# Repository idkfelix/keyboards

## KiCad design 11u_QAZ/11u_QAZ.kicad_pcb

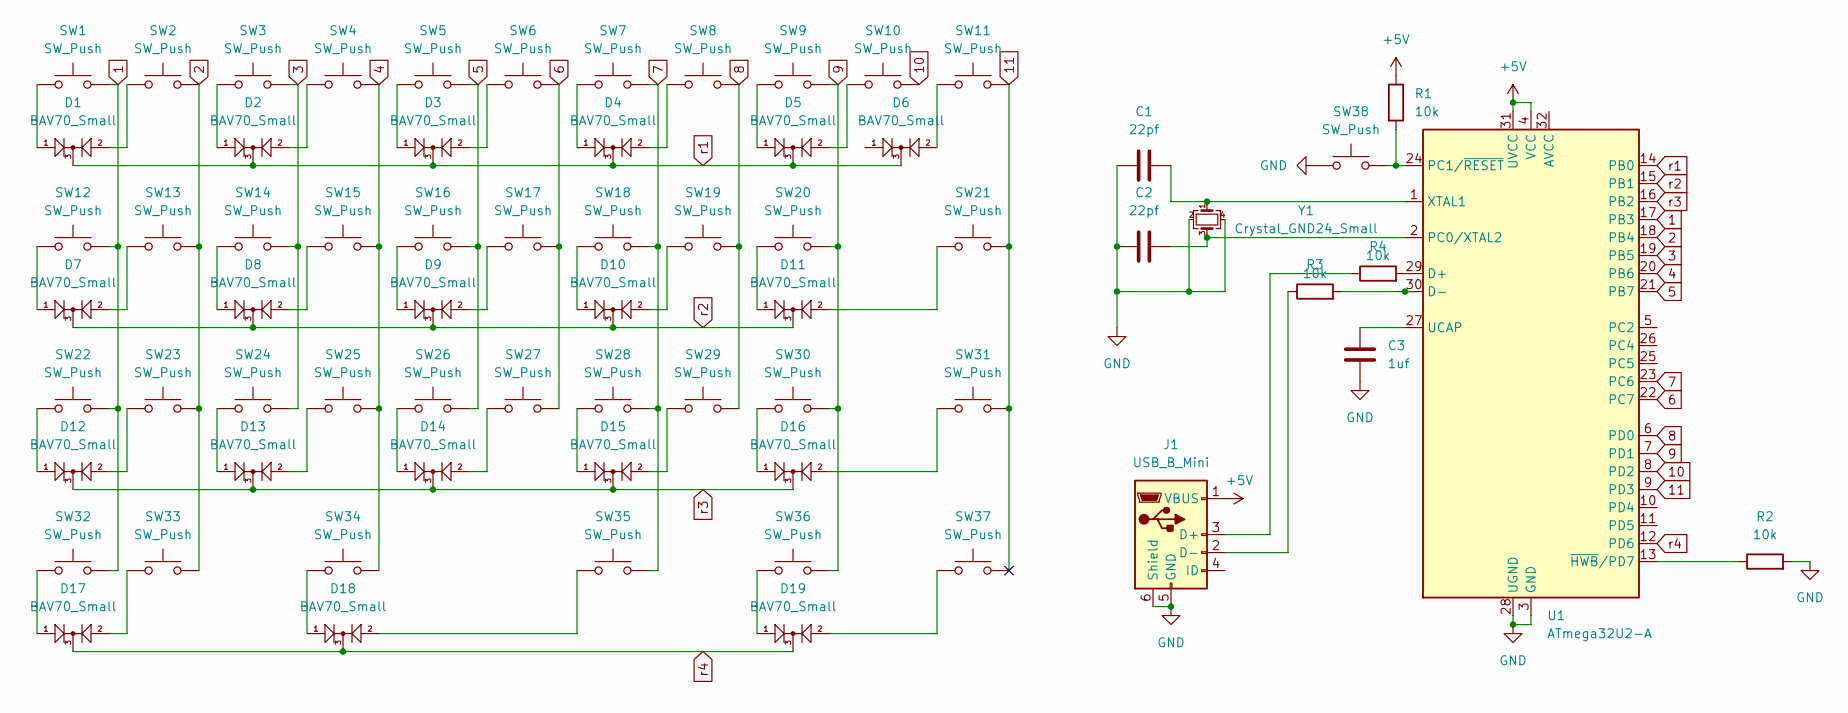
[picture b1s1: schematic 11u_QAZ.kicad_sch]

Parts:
C1, C2: 22pf; C_0805_2012Metric_Pad1.18x1.45mm_HandSolder
C3: 1uf; C_0805_2012Metric_Pad1.18x1.45mm_HandSolder
D1, D2, D3, D4, D5, D6, D7, D8, D9, D10, D11, D12, D13, D14, D15, D16, D17, D18, D19: BAV70_Small; SOT-23
J1: USB_B_Mini; Molex-0548190589
R1, R2, R3, R4: 10k; R_0805_2012Metric_Pad1.20x1.40mm_HandSolder
SW1, SW2, SW3, SW4, SW5, SW6, SW7, SW8, SW9, SW10, SW11, SW13, SW14, SW15, SW16, SW17, SW18, SW19, SW20, SW23, SW24, SW25, SW26, SW27, SW28, SW29, SW30: SW_Push; MX_1U
SW12, SW32, SW33, SW36, SW37: SW_Push; MX_1.25U
SW21: SW_Push; MX_1.75U
SW22, SW31: SW_Push; MX_1.5U
SW34: SW_Push; MX_2.75U
SW35: SW_Push; MX_2.25U
SW38: SW_Push; SKQG-1155865
U1: ATmega32U2-A; TQFP-32_7x7mm_P0.8mm
Y1: Crystal_GND24_Small; Crystal_SMD_3225-4Pin_3.2x2.5mm_HandSoldering

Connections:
1: SW1.1, SW12.1, SW22.1, SW32.1, U1.17 (PB3)
2: SW2.1, SW13.1, SW23.1, SW33.1, U1.18 (PB4)
3: SW3.1, SW14.1, SW24.1, U1.19 (PB5)
4: SW4.1, SW15.1, SW25.1, SW34.1, U1.20 (PB6)
5: SW5.1, SW16.1, SW26.1, U1.21 (PB7)
6: SW6.1, SW17.1, SW27.1, U1.22 (PC7)
7: SW7.1, SW18.1, SW28.1, SW35.1, U1.23 (PC6)
8: SW8.1, SW19.1, SW29.1, U1.6 (PD0)
9: SW9.1, SW20.1, SW30.1, SW36.1, U1.7 (PD1)
10: SW10.1, U1.8 (PD2)
11: SW11.1, SW21.1, SW31.1, SW37.1, U1.9 (PD3)
+5V: J1.1 (VBUS), R1.1, U1.4 (VCC), U1.31 (UVCC)
GND: C1.1, C2.1, C3.1, J1.5 (GND), J1.6 (Shield), R2.2, SW38.1, U1.3 (GND), U1.28 (UGND), Y1.2, Y1.4
unnamed: D1.1 (A1), SW1.2
unnamed: D1.2 (A2), SW2.2
unnamed: D2.1 (A1), SW3.2
unnamed: D2.2 (A2), SW4.2
unnamed: D3.1 (A1), SW5.2
unnamed: D3.2 (A2), SW6.2
unnamed: D4.1 (A1), SW7.2
unnamed: D4.2 (A2), SW8.2
unnamed: D5.1 (A1), SW9.2
unnamed: D5.2 (A2), SW10.2
unnamed: D6.2 (A2), SW11.2
unnamed: D7.1 (A1), SW12.2
unnamed: D7.2 (A2), SW13.2
unnamed: D8.1 (A1), SW14.2
unnamed: D8.2 (A2), SW15.2
unnamed: D9.1 (A1), SW16.2
unnamed: D9.2 (A2), SW17.2
unnamed: D10.1 (A1), SW18.2
unnamed: D10.2 (A2), SW19.2
unnamed: D11.1 (A1), SW20.2
unnamed: D11.2 (A2), SW21.2
unnamed: D12.1 (A1), SW22.2
unnamed: D12.2 (A2), SW23.2
unnamed: D13.1 (A1), SW24.2
unnamed: D13.2 (A2), SW25.2
unnamed: D14.1 (A1), SW26.2
unnamed: D14.2 (A2), SW27.2
unnamed: D15.1 (A1), SW28.2
unnamed: D15.2 (A2), SW29.2
unnamed: D16.1 (A1), SW30.2
unnamed: D16.2 (A2), SW31.2
unnamed: D17.1 (A1), SW32.2
unnamed: D17.2 (A2), SW33.2
unnamed: D18.1 (A1), SW34.2
unnamed: D18.2 (A2), SW35.2
unnamed: D19.1 (A1), SW36.2
unnamed: D19.2 (A2), SW37.2
unnamed: J1.3 (D+), R4.1
unnamed: J1.2 (D-), R3.1
unnamed: R4.2, U1.29 (D+)
unnamed: R3.2, U1.30 (D-)
unnamed: C2.2, U1.2 (PC0/XTAL2), Y1.3
unnamed: R1.2, SW38.2, U1.24 (PC1/~RESET)
unnamed: C3.2, U1.27 (UCAP)
unnamed: C1.2, U1.1 (XTAL1), Y1.1
unnamed: R2.1, U1.13 (~HWB/PD7)
r1: D1.3 (K), D2.3 (K), D3.3 (K), D4.3 (K), D5.3 (K), D6.3 (K), U1.14 (PB0)
r2: D7.3 (K), D8.3 (K), D9.3 (K), D10.3 (K), D11.3 (K), U1.15 (PB1)
r3: D12.3 (K), D13.3 (K), D14.3 (K), D15.3 (K), D16.3 (K), U1.16 (PB2)
r4: D17.3 (K), D18.3 (K), D19.3 (K), U1.12 (PD6)

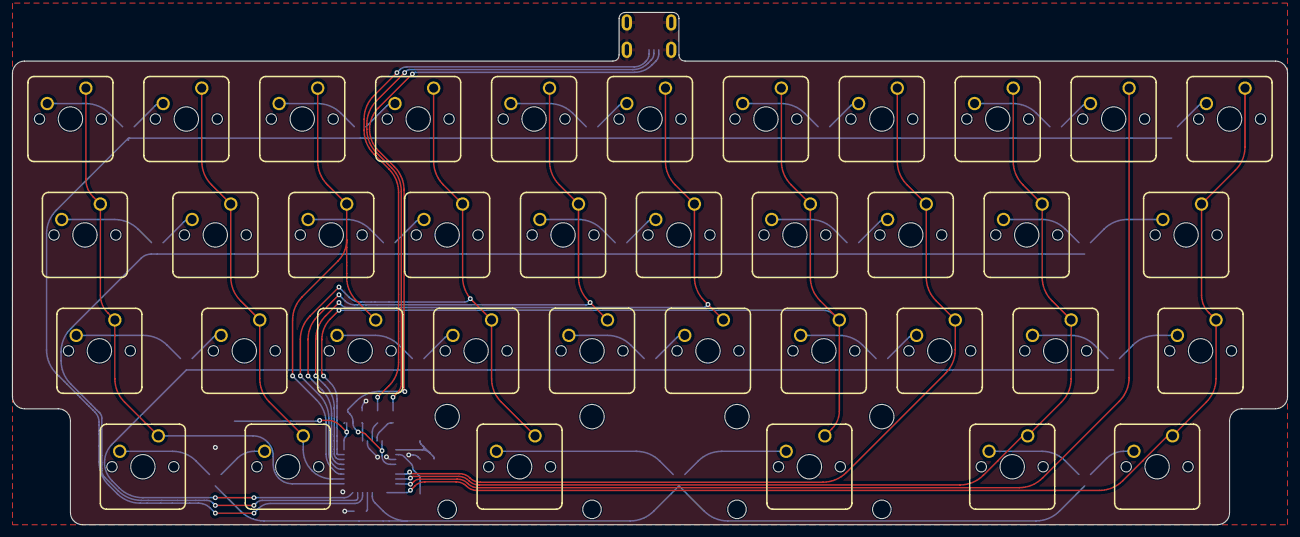
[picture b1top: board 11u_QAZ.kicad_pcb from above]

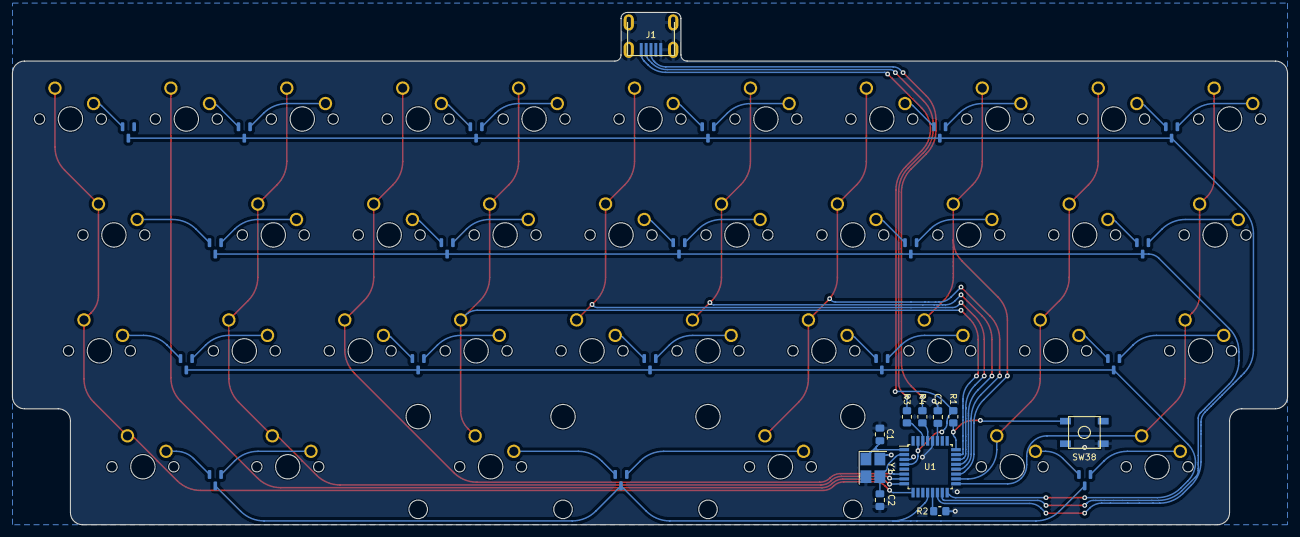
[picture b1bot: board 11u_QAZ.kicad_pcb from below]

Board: 2 copper layers, 209.5 x 84.2 mm, 67 parts (30 on the bottom side), 63 nets.

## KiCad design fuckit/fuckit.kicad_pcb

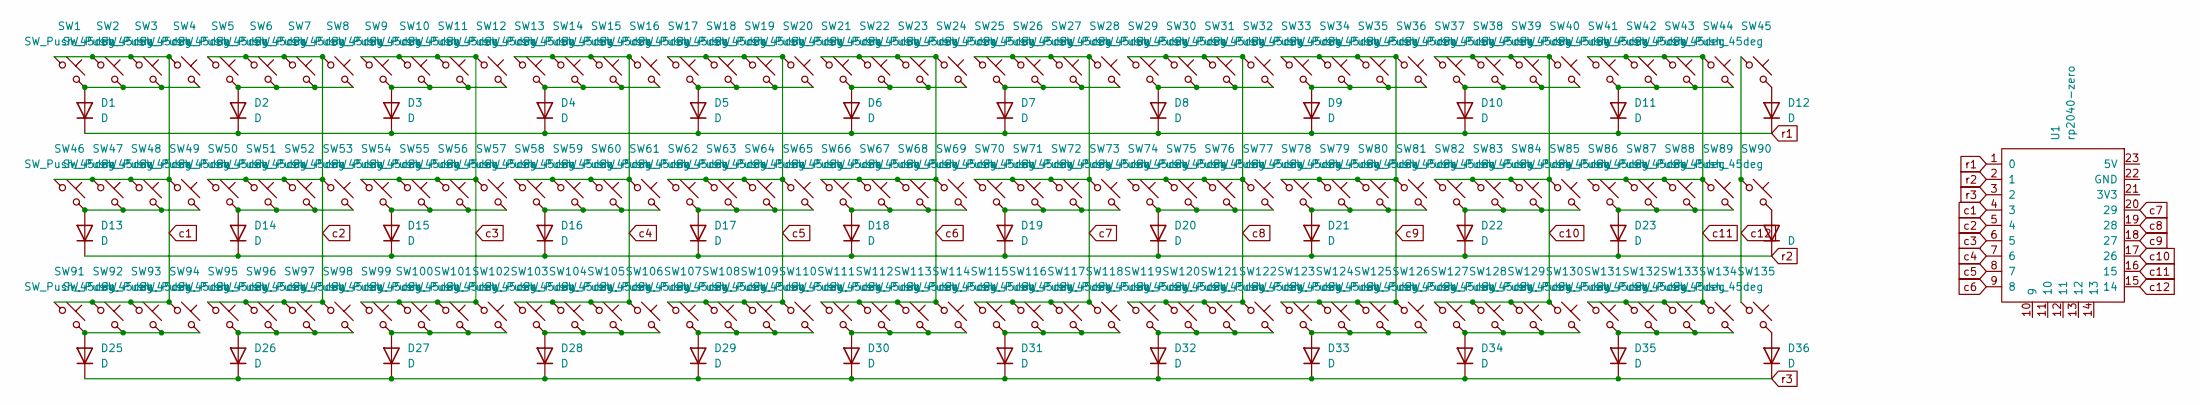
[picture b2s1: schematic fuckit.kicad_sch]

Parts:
D1, D2, D3, D4, D5, D6, D7, D8, D9, D10, D11, D12, D13, D14, D15, D16, D17, D18, D19, D20, D21, D22, D23, D24, D25, D26, D27, D28, D29, D30, D31, D32, D33, D34, D35, D36: D; D_SOD-123
SW1, SW2, SW3, SW4, SW5, SW6, SW7, SW8, SW9, SW10, SW11, SW12, SW13, SW14, SW15, SW16, SW17, SW18, SW19, SW20, SW21, SW22, SW23, SW24, SW25, SW26, SW27, SW28, SW29, SW30, SW31, SW32, SW33, SW34, SW35, SW36, SW37, SW38, SW39, SW40, SW41, SW42, SW43, SW44, SW45, SW46, SW47, SW48, SW49, SW50, SW51, SW52, SW53, SW54, SW55, SW56, SW57, SW58, SW59, SW60, SW61, SW62, SW63, SW64, SW65, SW66, SW67, SW68, SW69, SW70, SW71, SW72, SW73, SW74, SW75, SW76, SW77, SW78, SW79, SW80, SW81, SW82, SW83, SW84, SW85, SW86, SW87, SW88, SW89, SW90, SW91, SW92, SW93, SW94, SW95, SW96, SW97, SW98, SW99, SW100, SW101, SW102, SW103, SW104, SW105, SW106, SW107, SW108, SW109, SW110, SW111, SW112, SW113, SW114, SW115, SW116, SW117, SW118, SW119, SW120, SW121, SW122, SW123, SW124, SW125, SW126, SW127, SW128, SW129, SW130, SW131, SW132, SW133, SW134, SW135: SW_Push_45deg; MX_1U_noSilk
U1: rp2040-zero; rp2040-zero-tht-SidesOnly

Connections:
unnamed: D1.2 (A), SW1.2, SW2.2, SW3.2, SW4.2
unnamed: D2.2 (A), SW5.2, SW6.2, SW7.2, SW8.2
unnamed: D3.2 (A), SW9.2, SW10.2, SW11.2, SW12.2
unnamed: D4.2 (A), SW13.2, SW14.2, SW15.2, SW16.2
unnamed: D5.2 (A), SW17.2, SW18.2, SW19.2, SW20.2
unnamed: D6.2 (A), SW21.2, SW22.2, SW23.2, SW24.2
unnamed: D7.2 (A), SW25.2, SW26.2, SW27.2, SW28.2
unnamed: D8.2 (A), SW29.2, SW30.2, SW31.2, SW32.2
unnamed: D9.2 (A), SW33.2, SW34.2, SW35.2, SW36.2
unnamed: D10.2 (A), SW37.2, SW38.2, SW39.2, SW40.2
unnamed: D11.2 (A), SW41.2, SW42.2, SW43.2, SW44.2
unnamed: D12.2 (A), SW45.2
unnamed: D13.2 (A), SW46.2, SW47.2, SW48.2, SW49.2
unnamed: D14.2 (A), SW50.2, SW51.2, SW52.2, SW53.2
unnamed: D15.2 (A), SW54.2, SW55.2, SW56.2, SW57.2
unnamed: D16.2 (A), SW58.2, SW59.2, SW60.2, SW61.2
unnamed: D17.2 (A), SW62.2, SW63.2, SW64.2, SW65.2
unnamed: D18.2 (A), SW66.2, SW67.2, SW68.2, SW69.2
unnamed: D19.2 (A), SW70.2, SW71.2, SW72.2, SW73.2
unnamed: D20.2 (A), SW74.2, SW75.2, SW76.2, SW77.2
unnamed: D21.2 (A), SW78.2, SW79.2, SW80.2, SW81.2
unnamed: D22.2 (A), SW82.2, SW83.2, SW84.2, SW85.2
unnamed: D23.2 (A), SW86.2, SW87.2, SW88.2, SW89.2
unnamed: D24.2 (A), SW90.2
unnamed: D25.2 (A), SW91.2, SW92.2, SW93.2, SW94.2
unnamed: D26.2 (A), SW95.2, SW96.2, SW97.2, SW98.2
unnamed: D27.2 (A), SW99.2, SW100.2, SW101.2, SW102.2
unnamed: D28.2 (A), SW103.2, SW104.2, SW105.2, SW106.2
unnamed: D29.2 (A), SW107.2, SW108.2, SW109.2, SW110.2
unnamed: D30.2 (A), SW111.2, SW112.2, SW113.2, SW114.2
unnamed: D31.2 (A), SW115.2, SW116.2, SW117.2, SW118.2
unnamed: D32.2 (A), SW119.2, SW120.2, SW121.2, SW122.2
unnamed: D33.2 (A), SW123.2, SW124.2, SW125.2, SW126.2
unnamed: D34.2 (A), SW127.2, SW128.2, SW129.2, SW130.2
unnamed: D35.2 (A), SW131.2, SW132.2, SW133.2, SW134.2
unnamed: D36.2 (A), SW135.2
c1: SW1.1, SW2.1, SW3.1, SW4.1, SW46.1, SW47.1, SW48.1, SW49.1, SW91.1, SW92.1, SW93.1, SW94.1, U1.4 (3)
c2: SW5.1, SW6.1, SW7.1, SW8.1, SW50.1, SW51.1, SW52.1, SW53.1, SW95.1, SW96.1, SW97.1, SW98.1, U1.5 (4)
c3: SW9.1, SW10.1, SW11.1, SW12.1, SW54.1, SW55.1, SW56.1, SW57.1, SW99.1, SW100.1, SW101.1, SW102.1, U1.6 (5)
c4: SW13.1, SW14.1, SW15.1, SW16.1, SW58.1, SW59.1, SW60.1, SW61.1, SW103.1, SW104.1, SW105.1, SW106.1, U1.7 (6)
c5: SW17.1, SW18.1, SW19.1, SW20.1, SW62.1, SW63.1, SW64.1, SW65.1, SW107.1, SW108.1, SW109.1, SW110.1, U1.8 (7)
c6: SW21.1, SW22.1, SW23.1, SW24.1, SW66.1, SW67.1, SW68.1, SW69.1, SW111.1, SW112.1, SW113.1, SW114.1, U1.9 (8)
c7: SW25.1, SW26.1, SW27.1, SW28.1, SW70.1, SW71.1, SW72.1, SW73.1, SW115.1, SW116.1, SW117.1, SW118.1, U1.20 (29)
c8: SW29.1, SW30.1, SW31.1, SW32.1, SW74.1, SW75.1, SW76.1, SW77.1, SW119.1, SW120.1, SW121.1, SW122.1, U1.19 (28)
c9: SW33.1, SW34.1, SW35.1, SW36.1, SW78.1, SW79.1, SW80.1, SW81.1, SW123.1, SW124.1, SW125.1, SW126.1, U1.18 (27)
c10: SW37.1, SW38.1, SW39.1, SW40.1, SW82.1, SW83.1, SW84.1, SW85.1, SW127.1, SW128.1, SW129.1, SW130.1, U1.17 (26)
c11: SW41.1, SW42.1, SW43.1, SW44.1, SW86.1, SW87.1, SW88.1, SW89.1, SW131.1, SW132.1, SW133.1, SW134.1, U1.16 (15)
c12: SW45.1, SW90.1, SW135.1, U1.15 (14)
r1: D1.1 (K), D2.1 (K), D3.1 (K), D4.1 (K), D5.1 (K), D6.1 (K), D7.1 (K), D8.1 (K), D9.1 (K), D10.1 (K), D11.1 (K), D12.1 (K), U1.1 (0)
r2: D13.1 (K), D14.1 (K), D15.1 (K), D16.1 (K), D17.1 (K), D18.1 (K), D19.1 (K), D20.1 (K), D21.1 (K), D22.1 (K), D23.1 (K), D24.1 (K), U1.2 (1)
r3: D25.1 (K), D26.1 (K), D27.1 (K), D28.1 (K), D29.1 (K), D30.1 (K), D31.1 (K), D32.1 (K), D33.1 (K), D34.1 (K), D35.1 (K), D36.1 (K), U1.3 (2)

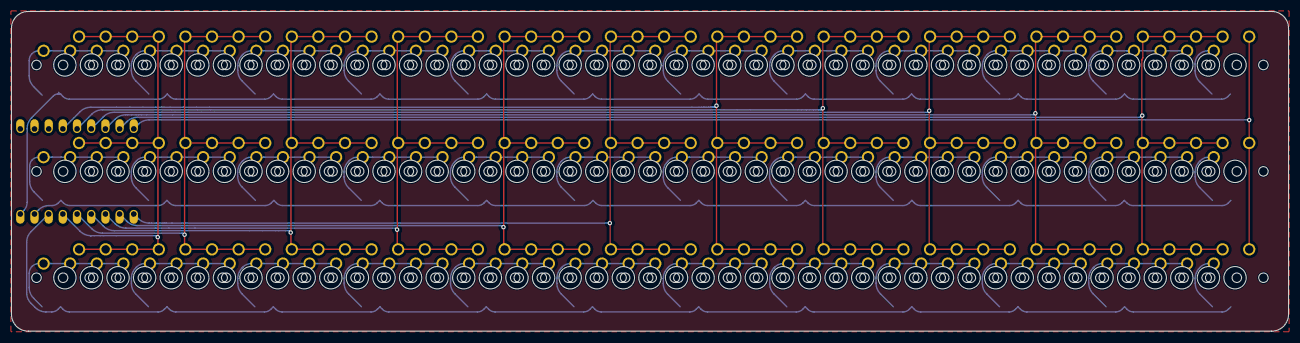
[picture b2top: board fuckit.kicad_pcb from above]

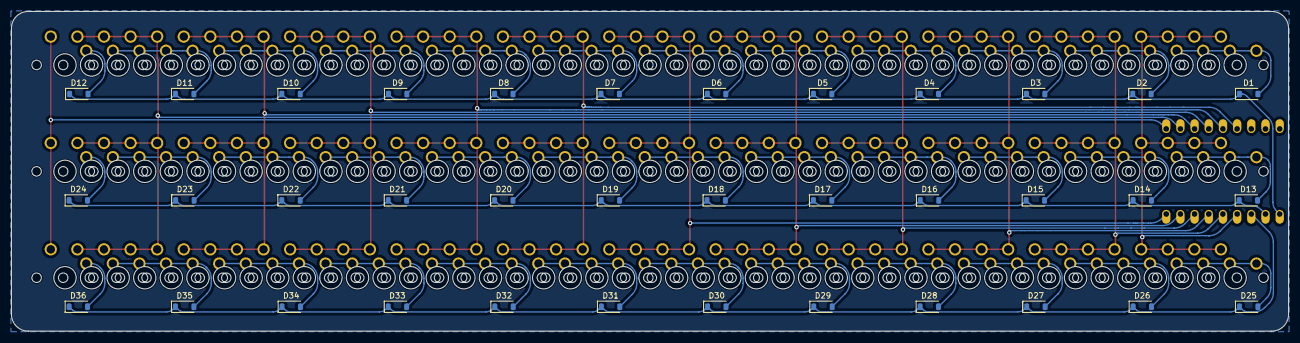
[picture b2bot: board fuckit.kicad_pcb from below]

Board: 2 copper layers, 228.7 x 57.2 mm, 172 parts (37 on the bottom side), 51 nets.

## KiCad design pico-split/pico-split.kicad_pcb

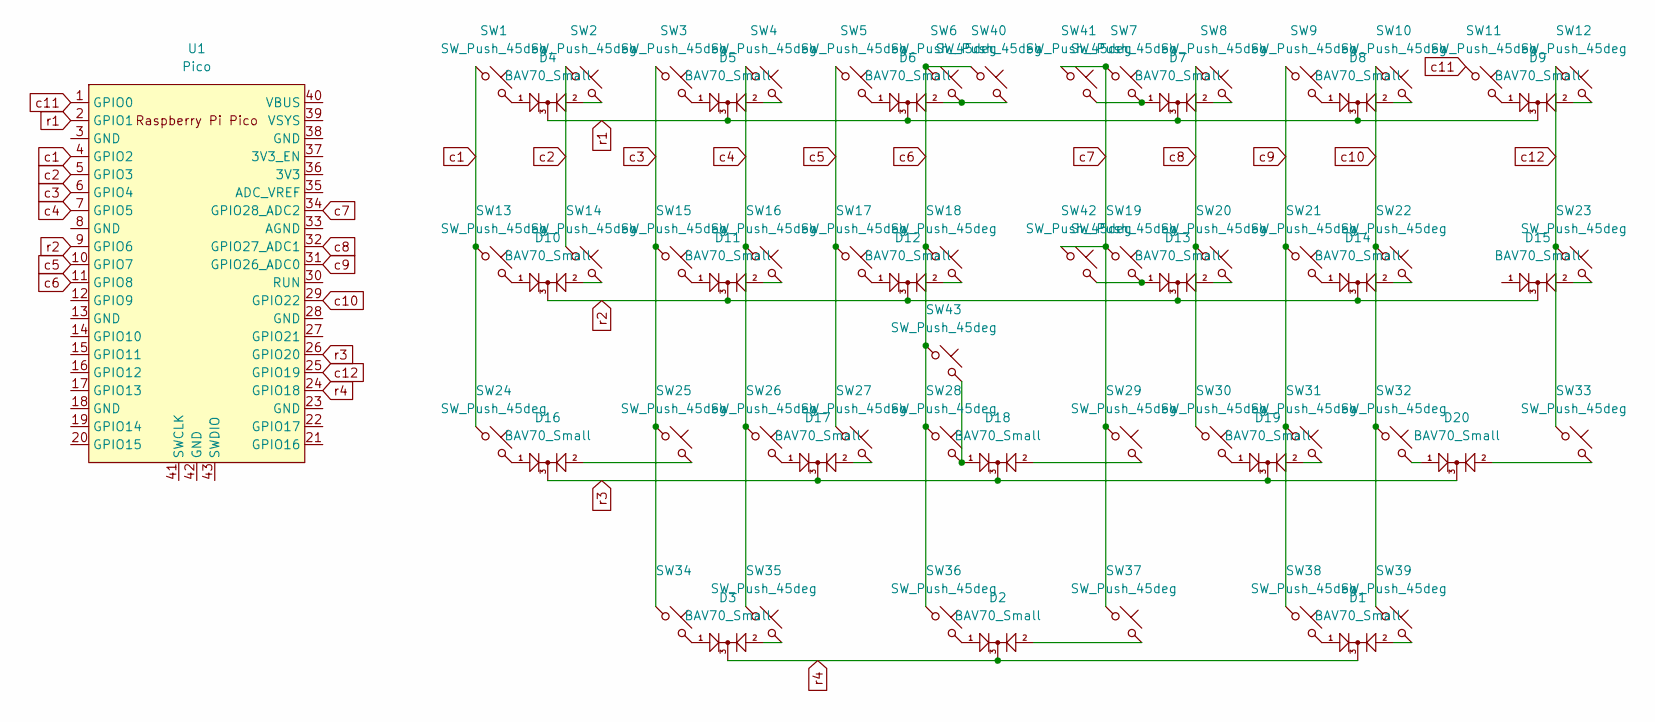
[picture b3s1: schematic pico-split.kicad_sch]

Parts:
D1, D2, D3, D4, D5, D6, D7, D8, D9, D10, D11, D12, D13, D14, D15, D16, D17, D18, D19, D20: BAV70_Small; SOT-23
SW1, SW2, SW3, SW4, SW5, SW8, SW9, SW10, SW11, SW12, SW14, SW15, SW16, SW17, SW18, SW20, SW21, SW22, SW25, SW26, SW27, SW28, SW29, SW30, SW31, SW32, SW40, SW41, SW42, SW43: SW_Push_45deg; MX_1U
SW6, SW7, SW13, SW34, SW35, SW38, SW39: SW_Push_45deg; MX_1.25U
SW19: SW_Push_45deg; MX_1.5U
SW23, SW24: SW_Push_45deg; MX_1.75U
SW33, SW36, SW37: SW_Push_45deg; MX_2.25U
U1: Pico; RPi_Pico_SMD_TH

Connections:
unnamed: D1.1 (A1), SW38.2
unnamed: D1.2 (A2), SW39.2
unnamed: D2.1 (A1), SW36.2
unnamed: D2.2 (A2), SW37.2
unnamed: D3.1 (A1), SW34.2
unnamed: D3.2 (A2), SW35.2
unnamed: D4.1 (A1), SW1.2
unnamed: D4.2 (A2), SW2.2
unnamed: D5.1 (A1), SW3.2
unnamed: D5.2 (A2), SW4.2
unnamed: D6.1 (A1), SW5.2
unnamed: D6.2 (A2), SW6.2, SW40.2
unnamed: D7.1 (A1), SW7.2, SW41.2
unnamed: D7.2 (A2), SW8.2
unnamed: D8.1 (A1), SW9.2
unnamed: D8.2 (A2), SW10.2
unnamed: D9.1 (A1), SW11.2
unnamed: D9.2 (A2), SW12.2
unnamed: D10.1 (A1), SW13.2
unnamed: D10.2 (A2), SW14.2
unnamed: D11.1 (A1), SW15.2
unnamed: D11.2 (A2), SW16.2
unnamed: D12.1 (A1), SW17.2
unnamed: D12.2 (A2), SW18.2
unnamed: D13.1 (A1), SW19.2, SW42.2
unnamed: D13.2 (A2), SW20.2
unnamed: D14.1 (A1), SW21.2
unnamed: D14.2 (A2), SW22.2
unnamed: D15.2 (A2), SW23.2
unnamed: D16.1 (A1), SW24.2
unnamed: D16.2 (A2), SW25.2
unnamed: D17.1 (A1), SW26.2
unnamed: D17.2 (A2), SW27.2
unnamed: D18.1 (A1), SW28.2, SW43.2
unnamed: D18.2 (A2), SW29.2
unnamed: D19.1 (A1), SW30.2
unnamed: D19.2 (A2), SW31.2
unnamed: D20.1 (A1), SW32.2
unnamed: D20.2 (A2), SW33.2
c1: SW1.1, SW13.1, SW24.1, U1.4 (GPIO2)
c2: SW2.1, SW14.1, U1.5 (GPIO3)
c3: SW3.1, SW15.1, SW25.1, SW34.1, U1.6 (GPIO4)
c4: SW4.1, SW16.1, SW26.1, SW35.1, U1.7 (GPIO5)
c5: SW5.1, SW17.1, SW27.1, U1.10 (GPIO7)
c6: SW6.1, SW18.1, SW28.1, SW36.1, SW40.1, SW43.1, U1.11 (GPIO8)
c7: SW7.1, SW19.1, SW29.1, SW37.1, SW41.1, SW42.1, U1.34 (GPIO28_ADC2)
c8: SW8.1, SW20.1, SW30.1, U1.32 (GPIO27_ADC1)
c9: SW9.1, SW21.1, SW31.1, SW38.1, U1.31 (GPIO26_ADC0)
c10: SW10.1, SW22.1, SW32.1, SW39.1, U1.29 (GPIO22)
c11: SW11.1, U1.1 (GPIO0)
c12: SW12.1, SW23.1, SW33.1, U1.25 (GPIO19)
r1: D4.3 (K), D5.3 (K), D6.3 (K), D7.3 (K), D8.3 (K), D9.3 (K), U1.2 (GPIO1)
r2: D10.3 (K), D11.3 (K), D12.3 (K), D13.3 (K), D14.3 (K), D15.3 (K), U1.9 (GPIO6)
r3: D16.3 (K), D17.3 (K), D18.3 (K), D19.3 (K), D20.3 (K), U1.26 (GPIO20)
r4: D1.3 (K), D2.3 (K), D3.3 (K), U1.24 (GPIO18)

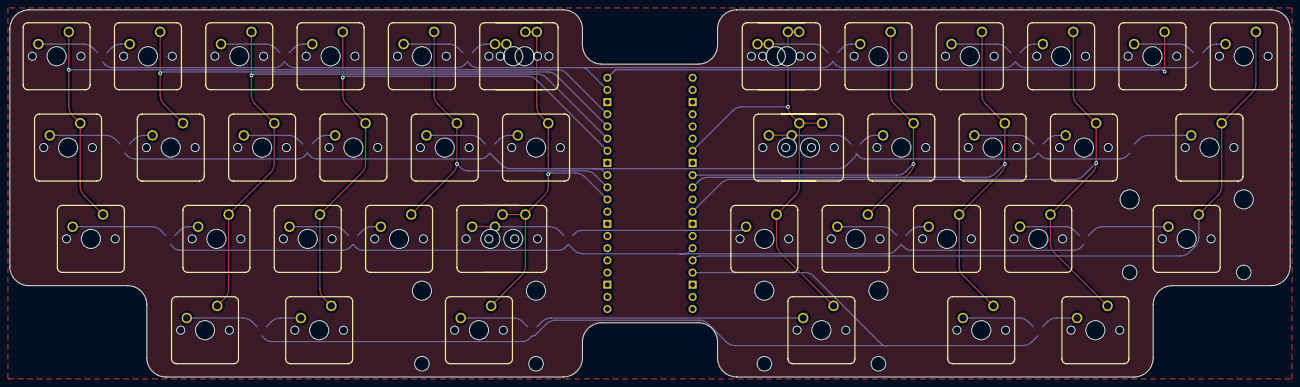
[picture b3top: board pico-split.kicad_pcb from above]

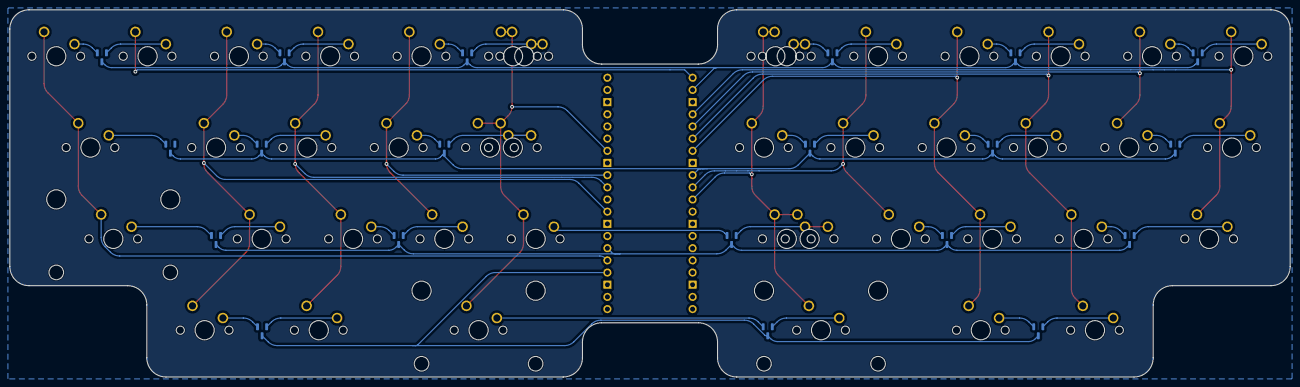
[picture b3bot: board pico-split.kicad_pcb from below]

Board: 2 copper layers, 267.1 x 76.6 mm, 64 parts (20 on the bottom side), 55 nets.

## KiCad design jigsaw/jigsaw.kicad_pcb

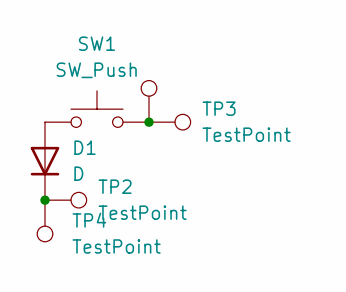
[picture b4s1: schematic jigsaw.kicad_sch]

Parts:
D1: D; D_0603_1608Metric
SW1: SW_Push; SW_Hotswap_Kailh_MX_1.00u
TP1, TP2: TestPoint; TestPoint_Pad_D2.5mm
TP3, TP4: TestPoint; TestPoint_Pad_D4.0mm

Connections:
unnamed: D1.2 (A), SW1.1
unnamed: D1.1 (K), TP2.1, TP4.1
unnamed: SW1.2, TP1.1, TP3.1

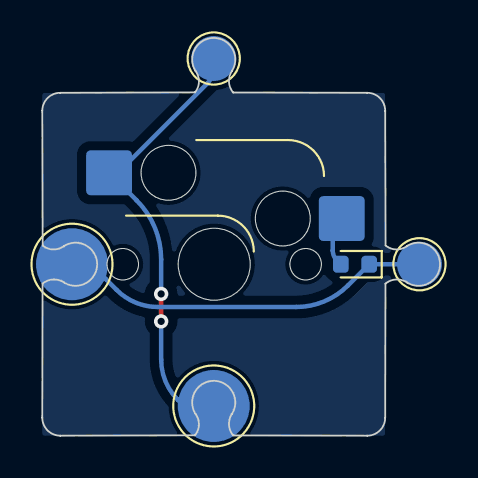
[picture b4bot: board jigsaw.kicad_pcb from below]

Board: 2 copper layers, 22.1 x 22.1 mm, 6 parts (5 on the bottom side), 3 nets.

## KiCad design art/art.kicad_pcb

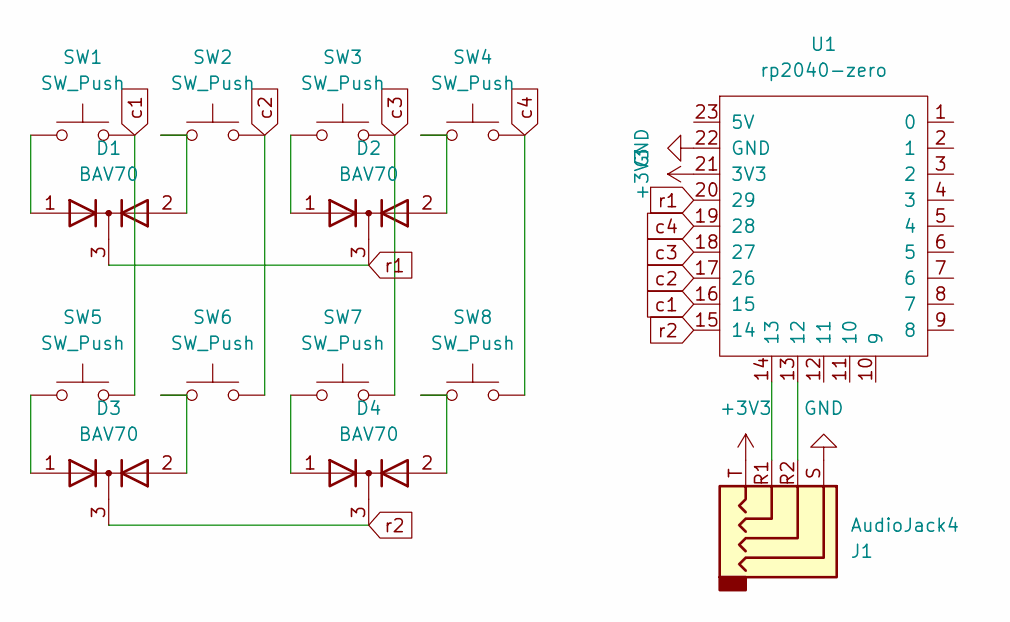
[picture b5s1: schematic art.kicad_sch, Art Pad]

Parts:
D1, D2, D3, D4: BAV70; SOT-23
J1: AudioJack4; CON_MJ-4PP-9_Reversible
SW1, SW2, SW3, SW4, SW5, SW6, SW7, SW8: SW_Push; SW_choc_Reversible_1u
U1: rp2040-zero; rp2040-zero-tht

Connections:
+3V3: J1.T, U1.21 (3V3)
GND: J1.S, U1.22 (GND)
unnamed: D1.1 (A), SW1.1
unnamed: D1.2 (A), SW2.1
unnamed: D2.1 (A), SW3.1
unnamed: D2.2 (A), SW4.1
unnamed: D3.1 (A), SW5.1
unnamed: D3.2 (A), SW6.1
unnamed: D4.1 (A), SW7.1
unnamed: D4.2 (A), SW8.1
unnamed: J1.R2, U1.13 (12)
unnamed: J1.R1, U1.14 (13)
c1: SW1.2, SW5.2, U1.16 (15)
c2: SW2.2, SW6.2, U1.17 (26)
c3: SW3.2, SW7.2, U1.18 (27)
c4: SW4.2, SW8.2, U1.19 (28)
r1: D1.3 (K), D2.3 (K), U1.20 (29)
r2: D3.3 (K), D4.3 (K), U1.15 (14)

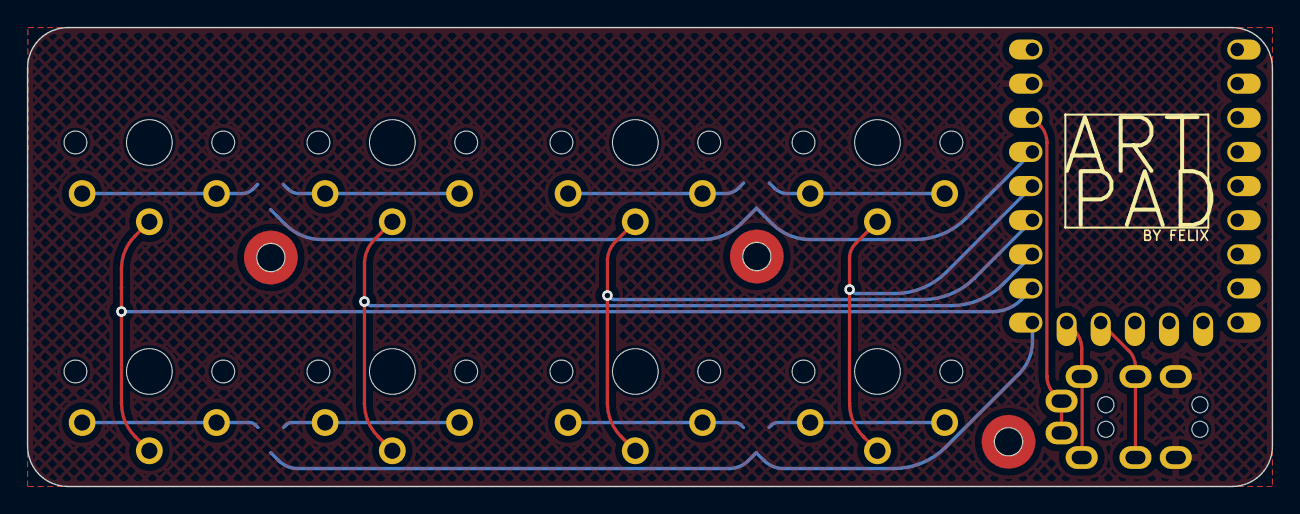
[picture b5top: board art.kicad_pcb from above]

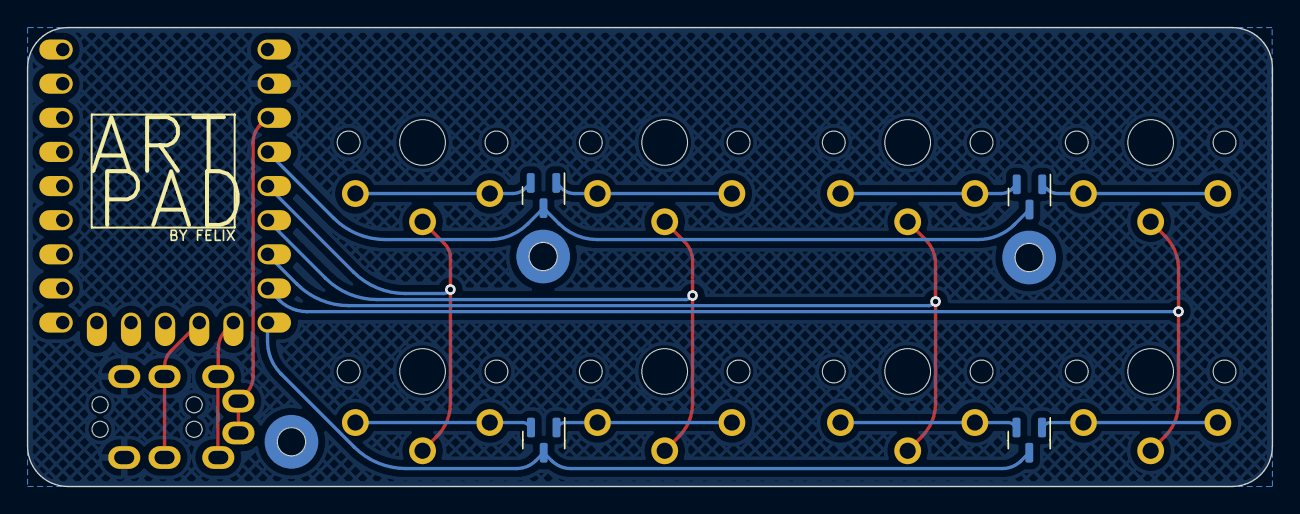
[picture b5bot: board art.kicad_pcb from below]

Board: 2 copper layers, 92.6 x 34.2 mm, 14 parts (4 on the bottom side), 18 nets.

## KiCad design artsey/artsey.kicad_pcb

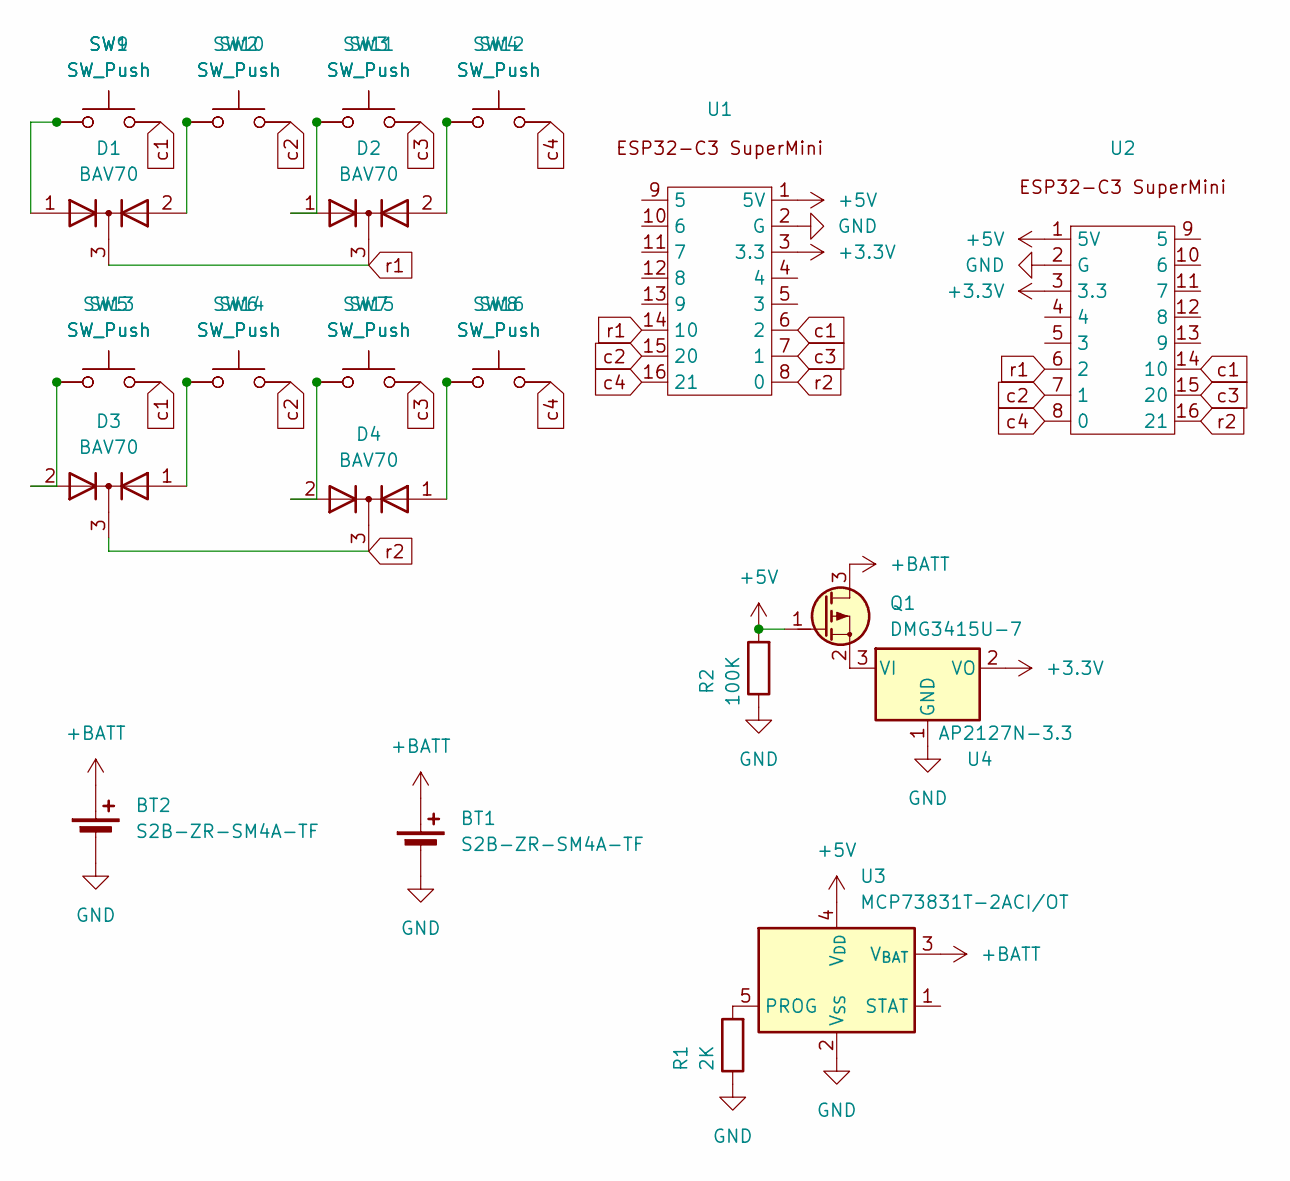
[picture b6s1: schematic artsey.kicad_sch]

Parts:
BT1, BT2: S2B-ZR-SM4A-TF; JST_PH_S2B-PH-SM4-TB_1x02-1MP_P2.00mm_Horizontal
D1, D2, D3, D4: BAV70; SOT-23
Q1: DMG3415U-7; SC-59
R1: 2K; R_0603_1608Metric
R2: 100K; R_0603_1608Metric
SW1, SW2, SW3, SW4, SW5, SW6, SW7, SW8: SW_Push; SW_choc_Reversible_1u
SW9, SW10, SW11, SW12, SW13, SW14, SW15, SW16: SW_Push; SW_MX_Reversible_1u
U1, U2: esp32-c3 superMini
U3: MCP73831T-2ACI/OT; SOT-23-5
U4: AP2127N-3.3; SOT-23

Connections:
+3.3V: U1.3 (3.3), U2.3 (3.3), U4.2 (VO)
+5V: Q1.1 (G), R2.2, U1.1 (5V), U2.1 (5V), U3.4 (V_{DD})
+BATT: BT1.1 (+), BT2.1 (+), Q1.3 (D), U3.3 (V_{BAT})
GND: BT1.2 (-), BT2.2 (-), R1.1, R2.1, U1.2 (G), U2.2 (G), U3.2 (V_{SS}), U4.1 (GND)
unnamed: D1.1 (A), SW1.1, SW9.1
unnamed: D1.2 (A), SW2.1, SW10.1
unnamed: D2.1 (A), SW3.1, SW11.1
unnamed: D2.2 (A), SW4.1, SW12.1
unnamed: D3.1 (A), SW6.1, SW14.1
unnamed: D3.2 (A), SW5.1, SW13.1
unnamed: D4.1 (A), SW8.1, SW16.1
unnamed: D4.2 (A), SW7.1, SW15.1
unnamed: Q1.2 (S), U4.3 (VI)
unnamed: R1.2, U3.5 (PROG)
c1: SW1.2, SW5.2, SW9.2, SW13.2, U1.6 (2), U2.14 (10)
c2: SW2.2, SW6.2, SW10.2, SW14.2, U1.15 (20), U2.7 (1)
c3: SW3.2, SW7.2, SW11.2, SW15.2, U1.7 (1), U2.15 (20)
c4: SW4.2, SW8.2, SW12.2, SW16.2, U1.16 (21), U2.8 (0)
r1: D1.3 (K), D2.3 (K), U1.14 (10), U2.6 (2)
r2: D3.3 (K), D4.3 (K), U1.8 (0), U2.16 (21)

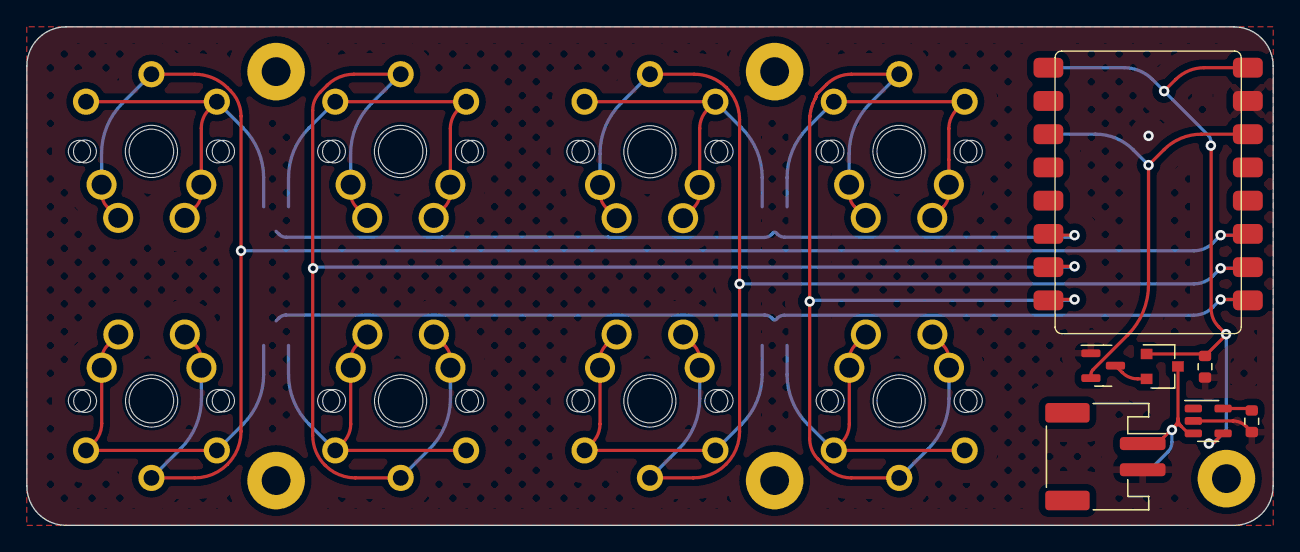
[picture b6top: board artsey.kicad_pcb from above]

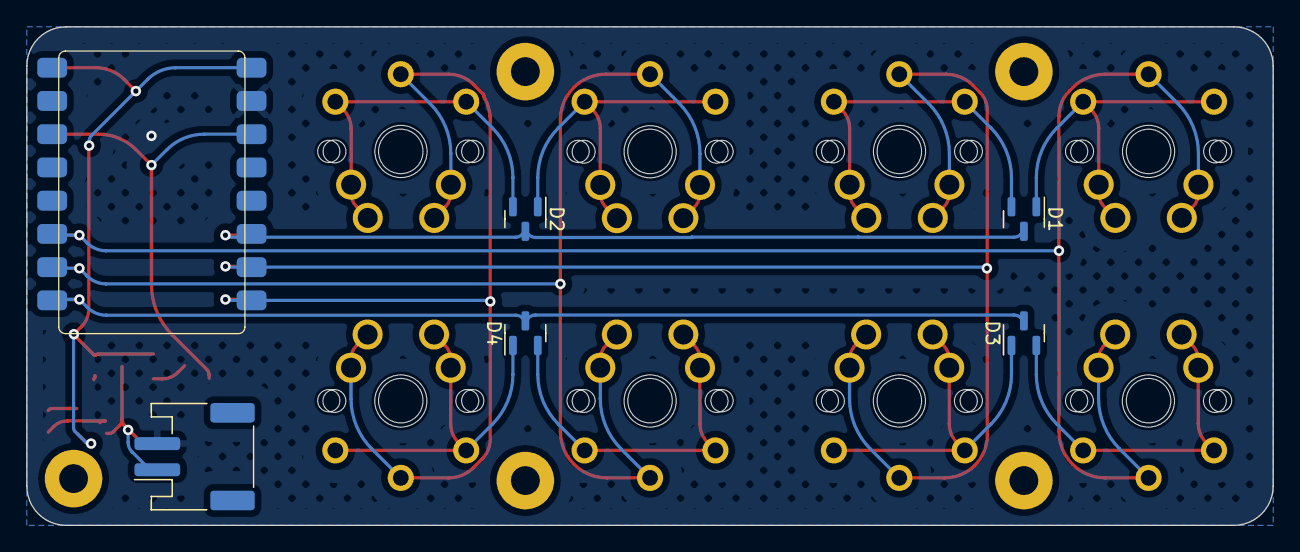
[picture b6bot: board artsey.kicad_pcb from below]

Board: 2 copper layers, 95.2 x 38.1 mm, 29 parts (6 on the bottom side), 20 nets.

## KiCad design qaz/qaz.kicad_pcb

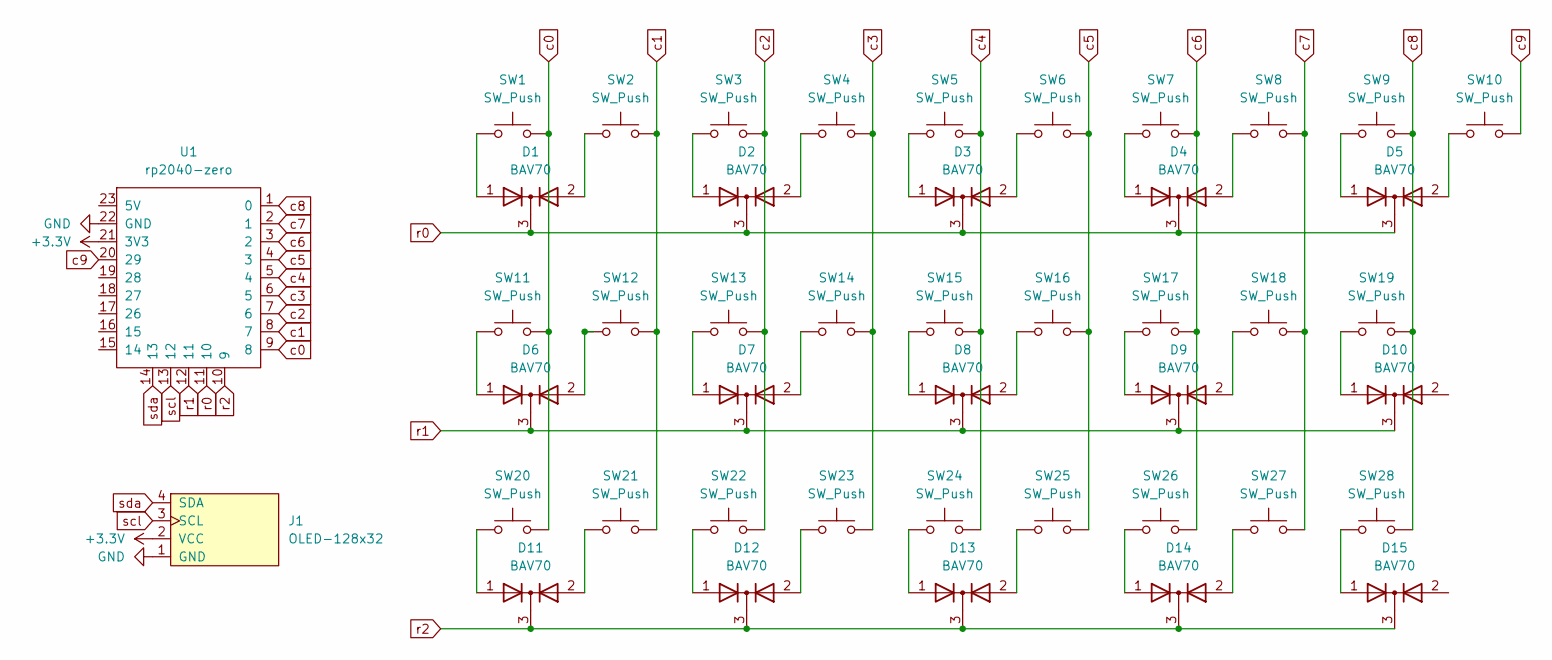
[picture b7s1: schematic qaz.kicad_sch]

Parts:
D1, D2, D3, D4, D5, D6, D7, D8, D9, D10, D11, D12, D13, D14, D15: BAV70; bav70
J1: OLED-128x32
SW1, SW2, SW3, SW4, SW5, SW6, SW7, SW8, SW9, SW10, SW11, SW12, SW13, SW14, SW15, SW16, SW17, SW18, SW19, SW20, SW21, SW22, SW23, SW24, SW25, SW26, SW27, SW28: SW_Push; SW_choc_MxCombo_1u
U1: rp2040-zero; rp2040-zero-smd

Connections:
+3.3V: J1.2 (VCC), U1.21 (3V3)
GND: J1.1 (GND), U1.22 (GND)
unnamed: D1.1 (A), SW1.1
unnamed: D1.2 (A), SW2.1
unnamed: D2.1 (A), SW3.1
unnamed: D2.2 (A), SW4.1
unnamed: D3.1 (A), SW5.1
unnamed: D3.2 (A), SW6.1
unnamed: D4.1 (A), SW7.1
unnamed: D4.2 (A), SW8.1
unnamed: D5.1 (A), SW9.1
unnamed: D5.2 (A), SW10.1
unnamed: D6.1 (A), SW11.1
unnamed: D6.2 (A), SW12.1
unnamed: D7.1 (A), SW13.1
unnamed: D7.2 (A), SW14.1
unnamed: D8.1 (A), SW15.1
unnamed: D8.2 (A), SW16.1
unnamed: D9.1 (A), SW17.1
unnamed: D9.2 (A), SW18.1
unnamed: D10.1 (A), SW19.1
unnamed: D11.1 (A), SW20.1
unnamed: D11.2 (A), SW21.1
unnamed: D12.1 (A), SW22.1
unnamed: D12.2 (A), SW23.1
unnamed: D13.1 (A), SW24.1
unnamed: D13.2 (A), SW25.1
unnamed: D14.1 (A), SW26.1
unnamed: D14.2 (A), SW27.1
unnamed: D15.1 (A), SW28.1
c0: SW1.2, SW11.2, SW20.2, U1.9 (8)
c1: SW2.2, SW12.2, SW21.2, U1.8 (7)
c2: SW3.2, SW13.2, SW22.2, U1.7 (6)
c3: SW4.2, SW14.2, SW23.2, U1.6 (5)
c4: SW5.2, SW15.2, SW24.2, U1.5 (4)
c5: SW6.2, SW16.2, SW25.2, U1.4 (3)
c6: SW7.2, SW17.2, SW26.2, U1.3 (2)
c7: SW8.2, SW18.2, SW27.2, U1.2 (1)
c8: SW9.2, SW19.2, SW28.2, U1.1 (0)
c9: SW10.2, U1.20 (29)
r0: D1.3 (K), D2.3 (K), D3.3 (K), D4.3 (K), D5.3 (K), U1.11 (10)
r1: D6.3 (K), D7.3 (K), D8.3 (K), D9.3 (K), D10.3 (K), U1.12 (11)
r2: D11.3 (K), D12.3 (K), D13.3 (K), D14.3 (K), D15.3 (K), U1.10 (9)
scl: J1.3 (SCL), U1.13 (12)
sda: J1.4 (SDA), U1.14 (13)
